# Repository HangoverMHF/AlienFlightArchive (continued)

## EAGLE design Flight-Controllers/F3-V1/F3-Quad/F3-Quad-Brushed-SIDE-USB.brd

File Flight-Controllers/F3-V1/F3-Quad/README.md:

## NOTE: This is an archival copy of the original CC BY-SA AlienFlight flight controllers. Preserved for posterity.

## F3 Quad Brushed V1 Flight Controller

The F3 Quad Brushed V1 is an experimental flight controller designed to pilot Quadcopters using 7mm-8.5mm brushed motors. It features an ARM STM32 F3 processor, built in side USB for easy firmware flashing, and parameter editing, MPU6050 Gyro/Accelerometer, 9.5A ESCs, and a built in Bind button for hassle free transmitter binding.

### F3 Quad Brushed V1 Example Picture 
(JMPR build pictured - Latest build uses tactile switches in place of jumpers)

#### F3 Quad Brushed V1 Specifications

* Cleanflight/Betaflight compatible
* STM32 F3 MCU
* MPU6050 accelerometer/gyro sensor unit
* 4x 9.5A brushed ESCs (Mosfets) - 2oz copper recommended
* Direct programming connection via Side USB
* (*) serial connection for external DSM2/DSMX sat receiver (e.g. Spektrum SAT, OrangeRx R100 or Lemon RX)
* Alternate PPM receiver connection (i.e. Deltang Rx31)
* Hardware bind button for easy binding
* Boot button for easy firmware flashing
* Motor connections oriented for self explanatory connection
* Dimensions: 26x30mm (use thin FR4 material for weight savings)
* Direct operation from an single cell lipo battery
* All components arranged on the top layer

#### Build Files and Resources:

Schematic and board design ➜ [F3 Quad Brushed V1 Eagle CAD Files](/Flight-Controllers/F3-V1/F3-Quad "F3 Quad Brushed V1 Eagle CAD Files") 

This bare board can be made at ➜ [OSH Park](https://oshpark.com/ "OSH Park")

Stencils can be made at ➜ [OSH Stencils](https://www.oshstencils.com/ "OSH Stencils")

_**THESE FILES ARE BEING PROVIDED ''AS IS'' WITHOUT ANY EXPRESS OR IMPLIED WARRANTIES.**_

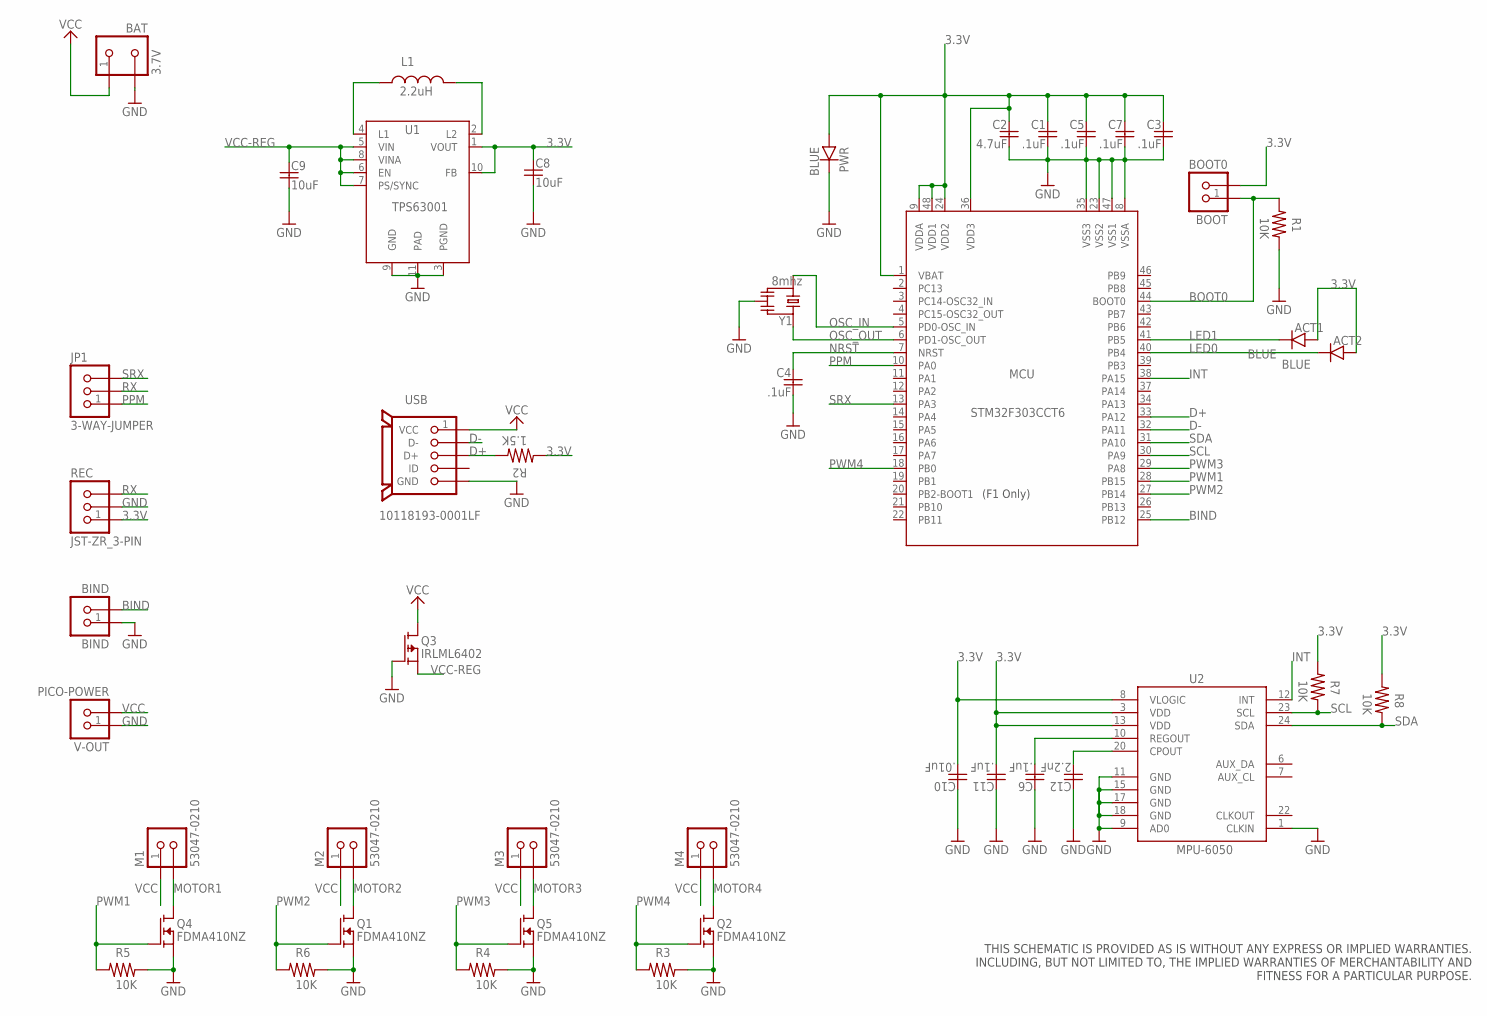
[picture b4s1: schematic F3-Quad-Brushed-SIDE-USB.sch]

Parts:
ACT1, ACT2: BLUE; SMD-CHIP-LED-0805
BAT: 3.7V; S2B-PH-K-S
BIND: BIND; B3U-1000P(M)
BOOT: BOOT0; B3U-1000P(M)
C1, C3, C4, C5, C6, C7, C11: .1uF; MUR-CAP-0603
C2: 4.7uF; MUR-CAP-0603
C8, C9: 10uF; YUDEN-CAP-0805
C10: .01uF; MUR-CAP-0603
C12: 2.2nF; MUR-CAP-0603
JP1: 3-WAY-JUMPER
L1: 2.2uH; NR301X
M1, M2, M3, M4: 53047-0210; PICO-53047-02
MCU: STM32F303CCT6; LQFP48-7X7
PWR: BLUE; SMD-CHIP-LED-0805
Q1, Q2, Q4, Q5: FDMA410NZ; MICROFET-2X2
Q3: IRLML6402; SOT-23
R1, R3, R4, R5, R6, R7, R8: 10K; VISH-RES-0603
R2: 1.5K; VISH-RES-0603
REC: JST-ZR_3-PIN; S3B-ZR
U1: TPS63001; VSON-N10
U2: MPU-6050; QFN24-4X4
USB: 10118193-0001LF
V-OUT: PICO-POWER; PICO_1.25_.5MM
Y1: 8mhz; RESONATOR_8

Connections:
3.3V: ACT1.A, ACT2.A, BOOT.2, C1.1, C2.1, C3.1, C5.1, C7.1, C8.1, C10.2, C11.2, MCU.1 (VBAT), MCU.9 (VDDA), MCU.24 (VDD2), MCU.36 (VDD3), MCU.48 (VDD1), PWR.A, R2.2, R7.2, R8.2, REC.1, U1.1 (VOUT), U1.10 (FB), U2.3 (VDD), U2.8 (VLOGIC), U2.13 (VDD)
BIND: BIND.2, MCU.25 (PB12)
BOOT0: BOOT.1, MCU.44 (BOOT0), R1.2
D+: MCU.33 (PA12), R2.1, USB.3 (D+)
D-: MCU.32 (PA11), USB.2 (D-)
GND: BAT.2, BIND.1, C1.2, C2.2, C3.2, C4.2, C5.2, C6.1, C7.2, C8.2, C9.2, C10.1, C11.1, C12.1, MCU.8 (VSSA), MCU.23 (VSS2), MCU.35 (VSS3), MCU.47 (VSS1), PWR.C, Q1.S, Q1.S1 (S), Q2.S, Q2.S1 (S), Q3.1 (G), Q4.S, Q4.S1 (S), Q5.S, Q5.S1 (S), R1.1, R3.1, R4.1, R5.1, R6.1, REC.2, U1.3 (PGND), U1.9 (GND), U1.11 (PAD), U2.1 (CLKIN), U2.9 (AD0), U2.11 (GND), U2.15 (GND), U2.17 (GND), U2.18 (GND), USB.5 (GND), USB.GND, USB.GND2 (GND), USB.HOLE1 (GND), USB.HOLE2 (GND), V-OUT.1, Y1.2
INT: MCU.38 (PA15), U2.12 (INT)
LED0: ACT2.C, MCU.40 (PB4)
LED1: ACT1.C, MCU.41 (PB5)
MOTOR1: M1.2, Q4.D, Q4.D1 (D), Q4.D2 (D), Q4.D3 (D), Q4.D4 (D)
MOTOR2: M2.2, Q1.D, Q1.D1 (D), Q1.D2 (D), Q1.D3 (D), Q1.D4 (D)
MOTOR3: M3.2, Q5.D, Q5.D1 (D), Q5.D2 (D), Q5.D3 (D), Q5.D4 (D)
MOTOR4: M4.2, Q2.D, Q2.D1 (D), Q2.D2 (D), Q2.D3 (D), Q2.D4 (D)
unnamed: C6.2, U2.10 (REGOUT)
unnamed: C12.2, U2.20 (CPOUT)
unnamed: L1.2, U1.2 (L2)
unnamed: L1.1, U1.4 (L1)
NRST: C4.1, MCU.7 (NRST)
OSC_IN: MCU.5 (PD0-OSC_IN), Y1.3
OSC_OUT: MCU.6 (PD1-OSC_OUT), Y1.1
PPM: JP1.1, MCU.10 (PA0)
PWM1: MCU.28 (PB15), Q4.G, R5.2
PWM2: MCU.27 (PB14), Q1.G, R6.2
PWM3: MCU.29 (PA8), Q5.G, R4.2
PWM4: MCU.18 (PB0), Q2.G, R3.2
RX: JP1.2, REC.3
SCL: MCU.30 (PA9), R7.1, U2.23 (SCL)
SDA: MCU.31 (PA10), R8.1, U2.24 (SDA)
SRX: JP1.3, MCU.13 (PA3)
VCC: BAT.1, M1.1, M2.1, M3.1, M4.1, Q3.3 (D), USB.1 (VCC), V-OUT.2
VCC-REG: C9.1, Q3.2 (S), U1.5 (VIN), U1.6 (EN), U1.7 (PS/SYNC), U1.8 (VINA)

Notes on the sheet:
THIS SCHEMATIC IS PROVIDED AS IS WITHOUT ANY EXPRESS OR IMPLIED WARRANTIES. INCLUDING, BUT NOT LIMITED TO, THE IMPLIED WARRANTIES OF MERCHANTABILITY AND FITNESS FOR A PARTICULAR PURPOSE.

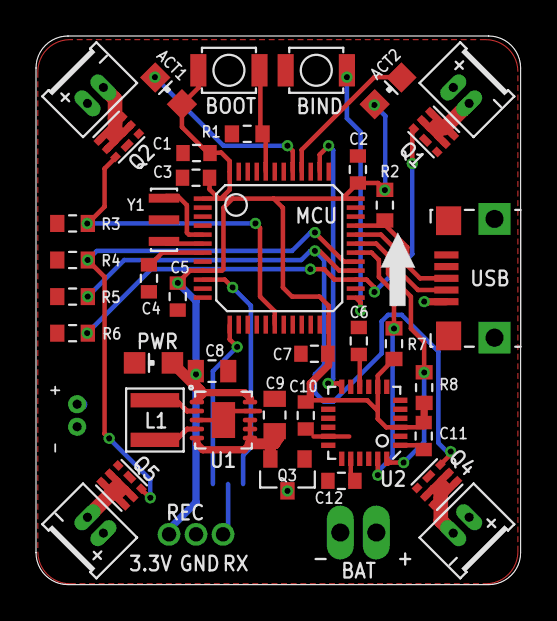
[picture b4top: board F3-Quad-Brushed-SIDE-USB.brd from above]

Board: 2 copper layers, 26.9 x 30.5 mm, 45 parts (1 on the bottom side), 31 nets.

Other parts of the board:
U$2: ARROW

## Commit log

2017-07-17 * Binary zip files arent' the best use of github revision control. Expanded into text and XML files. * TODO: ensure compatibility with latest version of Autodesk Eagle
2017-07-17 Removed PARTS.txt files which can be generated on-the-fly in Eagle
2017-07-17 Added a short explanatory note flagging this repository as archival
2017-07-17 * Many archival links result in 404 page not found. Replaced with links to OSH Park where board file can be uploaded to fabricate. Minor tidying..
2017-07-17 Archival export of AlienFlight library licensed under CC BY-SA 4.0
